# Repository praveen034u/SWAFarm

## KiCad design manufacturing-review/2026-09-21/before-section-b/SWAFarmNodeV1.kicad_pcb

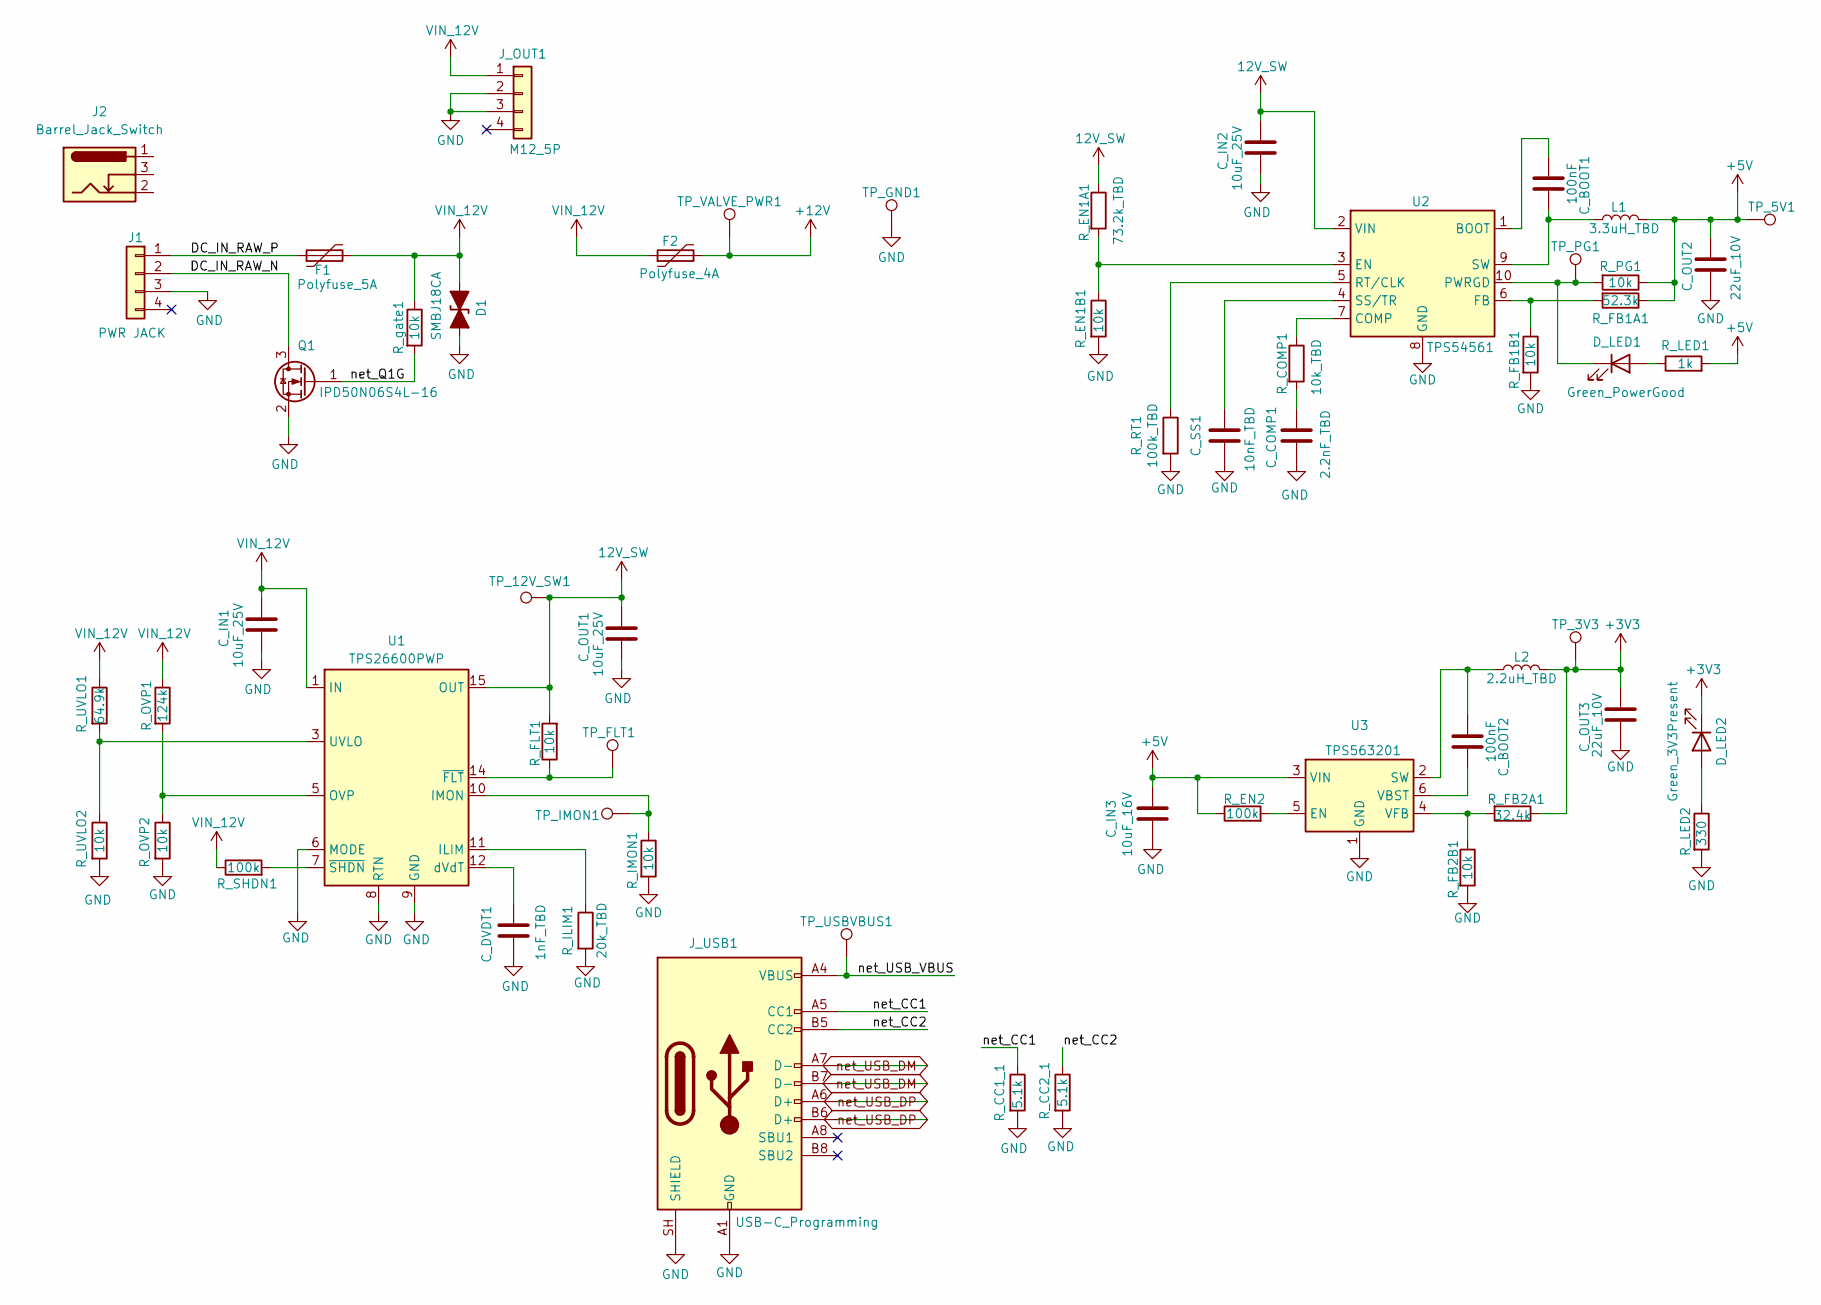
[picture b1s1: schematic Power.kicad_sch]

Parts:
C_BOOT1, C_BOOT2: 100nF; C_0603_1608Metric
C_COMP1: 2.2nF_TBD; C_0603_1608Metric
C_DVDT1: 1nF_TBD; C_0805_2012Metric
C_IN1, C_IN2: 10uF_25V; C_1206_3216Metric
C_IN3: 10uF_16V; C_1206_3216Metric
C_OUT1: 10uF_25V; C_1206_3216Metric
C_OUT2, C_OUT3: 22uF_10V; C_1206_3216Metric
C_SS1: 10nF_TBD; C_0603_1608Metric
D1: SMBJ18CA; D_SMB
D_LED1: Green_PowerGood; LED_0805_2012Metric
D_LED2: Green_3V3Present; LED_0805_2012Metric
F1: Polyfuse_5A; Fuse_1812_4532Metric
F2: Polyfuse_4A; Fuse_1812_4532Metric
J1: PWR JACK; PinHeader_1x04_P2.54mm_Vertical
J2: Barrel_Jack_Switch
J_OUT1: M12_5P; PinHeader_1x04_P2.54mm_Vertical
J_USB1: USB-C_Programming; USB_C_Receptacle_HRO_TYPE-C-31-M-12
L1: 3.3uH_TBD; L_Bourns-SRN6028
L2: 2.2uH_TBD; L_Bourns-SRN4018
Q1: IPD50N06S4L-16; SOT-23
R_CC1_1, R_CC2_1: 5.1k; R_0805_2012Metric
R_COMP1: 10k_TBD; R_0805_2012Metric
R_EN1A1: 73.2k_TBD; R_0805_2012Metric
R_EN1B1: 10k; R_0805_2012Metric
R_EN2: 100k; R_0805_2012Metric
R_FB1A1: 52.3k; R_0805_2012Metric
R_FB1B1, R_FB2B1: 10k; R_0805_2012Metric
R_FB2A1: 32.4k; R_0805_2012Metric
R_FLT1: 10k; R_0805_2012Metric
R_ILIM1: 20k_TBD; R_0805_2012Metric
R_IMON1: 10k; R_0805_2012Metric
R_LED1: 1k; R_0805_2012Metric
R_LED2: 330; R_0805_2012Metric
R_OVP1: 124k; R_0805_2012Metric
R_OVP2: 10k; R_0805_2012Metric
R_PG1: 10k; R_0805_2012Metric
R_RT1: 100k_TBD; R_0805_2012Metric
R_SHDN1: 100k; R_0805_2012Metric
R_UVLO1: 64.9k; R_0805_2012Metric
R_UVLO2: 10k; R_0805_2012Metric
R_gate1: 10k; R_0805_2012Metric
TP_3V3: V3V3_RAIL; TestPoint_Pad_D1.5mm
TP_5V1: V5_RAIL; TestPoint_Pad_D1.5mm
TP_12V_SW1: V12_SW; TestPoint_Pad_D1.5mm
TP_FLT1: nFLT; TestPoint_Pad_D1.5mm
TP_GND1: GND; TestPoint_Pad_D1.5mm
TP_IMON1: IMON; TestPoint_Pad_D1.5mm
TP_PG1: nPWRGD; TestPoint_Pad_D1.5mm
TP_USBVBUS1: USB_VBUS; TestPoint_Pad_D1.5mm
TP_VALVE_PWR1: V12_VALVE; TestPoint_Pad_D1.5mm
U1: TPS26600PWP; HTSSOP-16-1EP_4.4x5mm_P0.65mm_EP3.4x5mm_Mask2.66x2.46mm_The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
U2: TPS54561; WSON-10-1EP_4x4mm_P0.8mm_EP2.6x3mm_ThermalVias
U3: TPS563201; SOT-23-6

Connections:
12V_SW: C_IN2.1, C_OUT1.1, R_EN1A1.1, R_FLT1.2, TP_12V_SW1.1 (1_1), U1.15 (OUT), U1.16 (OUT), U2.2 (VIN)
+3V3: C_OUT3.1, D_LED2.1 (K), L2.2, R_FB2A1.1, TP_3V3.1 (1_1); also elsewhere on the board
+5V: C_IN3.1, C_OUT2.1, L1.2, R_EN2.1, R_FB1A1.1, R_LED1.2, R_PG1.1, TP_5V1.1 (1_1), U3.3 (VIN); also elsewhere on the board
+12V: F2.2, TP_VALVE_PWR1.1 (1_1); also elsewhere on the board
/Power/DC_IN_RAW_N: J1.2, Q1.3 (D)
/Power/DC_IN_RAW_P: F1.1, J1.1
/Power/net_CC1: J_USB1.A5 (CC1), R_CC1_1.1
/Power/net_CC2: J_USB1.B5 (CC2), R_CC2_1.1
/Power/net_Q1G: Q1.1 (G), R_gate1.2
/Power/net_USB_VBUS: J_USB1.A4 (VBUS), J_USB1.A9 (VBUS), J_USB1.B4 (VBUS), J_USB1.B9 (VBUS), TP_USBVBUS1.1 (1_1)
GND: C_COMP1.2, C_DVDT1.2, C_IN1.2, C_IN2.2, C_IN3.2, C_OUT1.2, C_OUT2.2, C_OUT3.2, C_SS1.2, D1.2 (A2), J1.3, J_OUT1.2, J_OUT1.3, J_USB1.A1 (GND), J_USB1.A12 (GND), J_USB1.B1 (GND), J_USB1.B12 (GND), J_USB1.SH (SHIELD), Q1.2 (S), R_CC1_1.2, R_CC2_1.2, R_EN1B1.2, R_FB1B1.2, R_FB2B1.2, R_ILIM1.2, R_IMON1.2, R_LED2.2, R_OVP2.2, R_RT1.2, R_UVLO2.2, TP_GND1.1 (1_1), U1.6 (MODE), U1.8 (RTN), U1.9 (GND), U1.17 (RTN), U2.8 (GND), U2.11 (GND), U3.1 (GND); also elsewhere on the board
unnamed: C_COMP1.1, R_COMP1.2
unnamed: D_LED1.2 (A), R_LED1.1
unnamed: D_LED1.1 (K), R_PG1.2, TP_PG1.1 (1_1), U2.10 (PWRGD)
unnamed: D_LED2.2 (A), R_LED2.1
unnamed: R_ILIM1.1, U1.11 (ILIM)
unnamed: R_IMON1.1, TP_IMON1.1 (1_1), U1.10 (IMON)
unnamed: R_OVP1.2, R_OVP2.1, U1.5 (OVP)
unnamed: R_UVLO1.2, R_UVLO2.1, U1.3 (UVLO)
unnamed: C_DVDT1.1, U1.12 (dVdT)
unnamed: R_FLT1.1, TP_FLT1.1 (1_1), U1.14 (~FLT)
unnamed: R_SHDN1.2, U1.7 (~SHDN)
unnamed: C_BOOT1.1, U2.1 (BOOT)
unnamed: R_COMP1.1, U2.7 (COMP)
unnamed: R_EN1A1.2, R_EN1B1.1, U2.3 (EN)
unnamed: R_FB1A1.2, R_FB1B1.1, U2.6 (FB)
unnamed: R_RT1.1, U2.5 (RT/CLK)
unnamed: C_SS1.1, U2.4 (SS/TR)
unnamed: C_BOOT1.2, L1.1, U2.9 (SW)
unnamed: R_EN2.2, U3.5 (EN)
unnamed: C_BOOT2.2, L2.1, U3.2 (SW)
unnamed: C_BOOT2.1, U3.6 (VBST)
unnamed: R_FB2A1.2, R_FB2B1.1, U3.4 (VFB)
VIN_12V: C_IN1.1, D1.1 (A1), F1.2, F2.1, J_OUT1.1, R_OVP1.1, R_SHDN1.1, R_UVLO1.1, R_gate1.1, U1.1 (IN), U1.2 (IN)
net_USB_DM: J_USB1.A7 (D-), J_USB1.B7 (D-); also elsewhere on the board
net_USB_DP: J_USB1.A6 (D+), J_USB1.B6 (D+); also elsewhere on the board

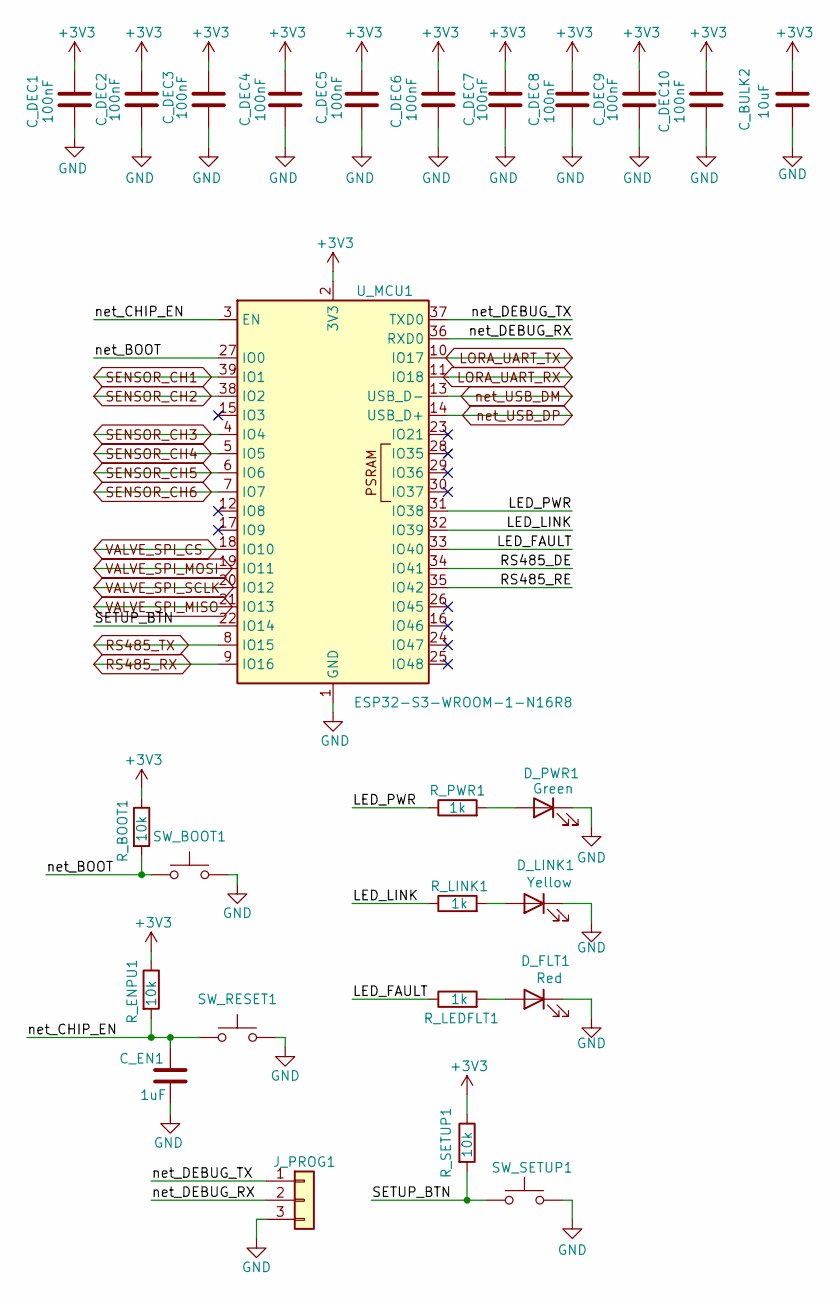
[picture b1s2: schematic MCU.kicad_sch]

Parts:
C_BULK2: 10uF; C_1206_3216Metric
C_DEC1, C_DEC2, C_DEC3, C_DEC4, C_DEC5, C_DEC6, C_DEC7, C_DEC8, C_DEC9, C_DEC10: 100nF; C_0603_1608Metric
C_EN1: 1uF; C_0805_2012Metric
D_FLT1: Red; LED_0805_2012Metric
D_LINK1: Yellow; LED_0805_2012Metric
D_PWR1: Green; LED_0805_2012Metric
J_PROG1: Debug_UART_TX_RX_GND; PinHeader_1x03_P2.54mm_Vertical
R_BOOT1: 10k; R_0805_2012Metric
R_ENPU1: 10k; R_0805_2012Metric
R_LEDFLT1: 1k; R_0805_2012Metric
R_LINK1: 1k; R_0805_2012Metric
R_PWR1: 1k; R_0805_2012Metric
R_SETUP1: 10k; R_0805_2012Metric
SW_BOOT1: BOOT; SW_SPST_B3U-1000P
SW_RESET1: RESET; SW_SPST_B3U-1000P
SW_SETUP1: SETUP; SW_SPST_B3U-1000P
U_MCU1: ESP32-S3-WROOM-1-N16R8; ESP32-S3-WROOM-1

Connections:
+3V3: C_BULK2.1, C_DEC1.1, C_DEC2.1, C_DEC3.1, C_DEC4.1, C_DEC5.1, C_DEC6.1, C_DEC7.1, C_DEC8.1, C_DEC9.1, C_DEC10.1, R_BOOT1.1, R_ENPU1.1, R_SETUP1.1, U_MCU1.2 (3V3); also elsewhere on the board
/MCU/LED_FAULT: R_LEDFLT1.1, U_MCU1.33 (IO40)
/MCU/LED_LINK: R_LINK1.1, U_MCU1.32 (IO39)
/MCU/LED_PWR: R_PWR1.1, U_MCU1.31 (IO38)
/MCU/RS485_DE: U_MCU1.34 (IO41)
/MCU/RS485_RE: U_MCU1.35 (IO42)
/MCU/SETUP_BTN: R_SETUP1.2, SW_SETUP1.1, U_MCU1.22 (IO14)
/MCU/net_BOOT: R_BOOT1.2, SW_BOOT1.1, U_MCU1.27 (IO0)
/MCU/net_CHIP_EN: C_EN1.1, R_ENPU1.2, SW_RESET1.1, U_MCU1.3 (EN)
/MCU/net_DEBUG_RX: J_PROG1.2, U_MCU1.36 (RXD0)
/MCU/net_DEBUG_TX: J_PROG1.1, U_MCU1.37 (TXD0)
GND: C_BULK2.2, C_DEC1.2, C_DEC2.2, C_DEC3.2, C_DEC4.2, C_DEC5.2, C_DEC6.2, C_DEC7.2, C_DEC8.2, C_DEC9.2, C_DEC10.2, C_EN1.2, D_FLT1.1 (K), D_LINK1.1 (K), D_PWR1.1 (K), J_PROG1.3, SW_BOOT1.2, SW_RESET1.2, SW_SETUP1.2, U_MCU1.1 (GND), U_MCU1.40 (GND), U_MCU1.41 (GND); also elsewhere on the board
LORA_UART_RX: U_MCU1.11 (IO18); also elsewhere on the board
LORA_UART_TX: U_MCU1.10 (IO17); also elsewhere on the board
unnamed: D_FLT1.2 (A), R_LEDFLT1.2
unnamed: D_LINK1.2 (A), R_LINK1.2
unnamed: D_PWR1.2 (A), R_PWR1.2
RS485_RX: U_MCU1.9 (IO16); also elsewhere on the board
RS485_TX: U_MCU1.8 (IO15); also elsewhere on the board
SENSOR_CH1: U_MCU1.39 (IO1); also elsewhere on the board
SENSOR_CH2: U_MCU1.38 (IO2); also elsewhere on the board
SENSOR_CH3: U_MCU1.4 (IO4); also elsewhere on the board
SENSOR_CH4: U_MCU1.5 (IO5); also elsewhere on the board
SENSOR_CH5: U_MCU1.6 (IO6); also elsewhere on the board
SENSOR_CH6: U_MCU1.7 (IO7); also elsewhere on the board
VALVE_SPI_CS: U_MCU1.18 (IO10); also elsewhere on the board
VALVE_SPI_MISO: U_MCU1.21 (IO13); also elsewhere on the board
VALVE_SPI_MOSI: U_MCU1.19 (IO11); also elsewhere on the board
VALVE_SPI_SCLK: U_MCU1.20 (IO12); also elsewhere on the board
net_USB_DM: U_MCU1.13 (USB_D-); also elsewhere on the board
net_USB_DP: U_MCU1.14 (USB_D+); also elsewhere on the board

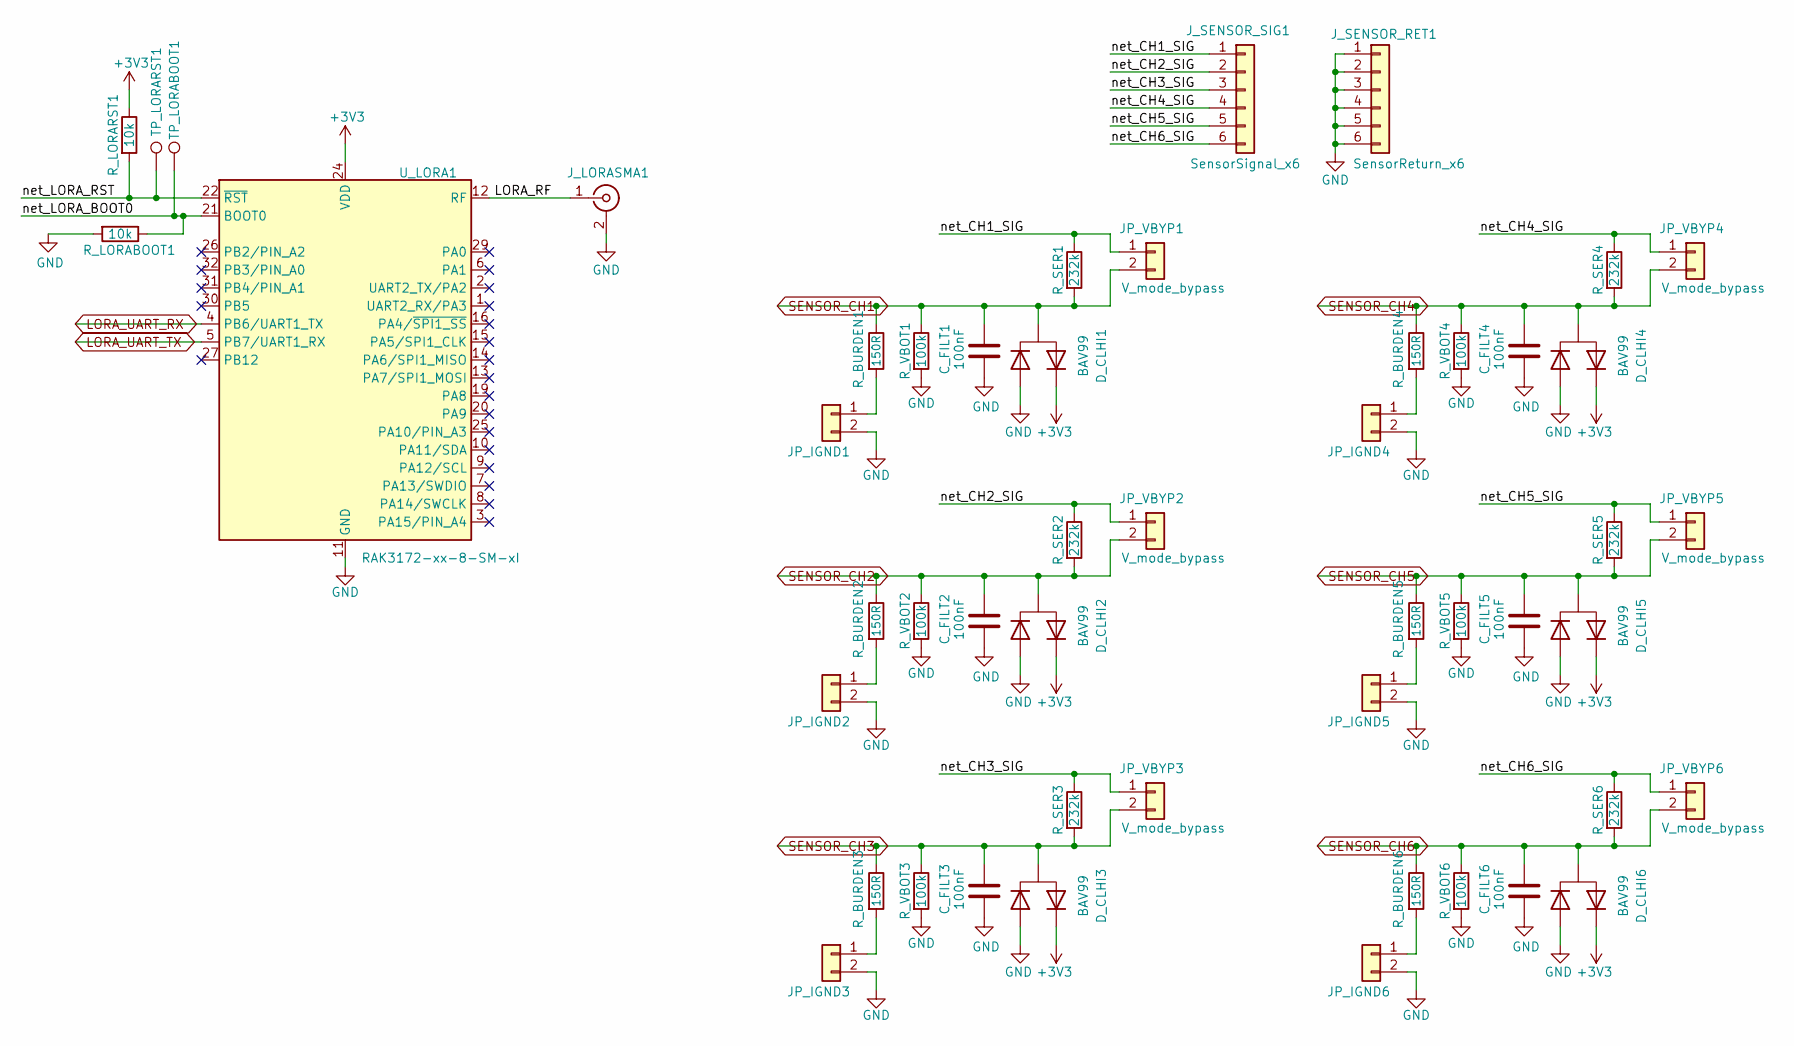
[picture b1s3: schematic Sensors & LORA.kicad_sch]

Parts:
C_FILT1, C_FILT2, C_FILT3, C_FILT4, C_FILT5, C_FILT6: 100nF; C_0603_1608Metric
D_CLHI1, D_CLHI2, D_CLHI3, D_CLHI4, D_CLHI5, D_CLHI6: BAV99; SOT-23
JP_IGND1, JP_IGND2, JP_IGND3, JP_IGND4, JP_IGND5, JP_IGND6: I_mode_gnd; PinHeader_1x02_P2.54mm_Vertical
JP_VBYP1, JP_VBYP2, JP_VBYP3, JP_VBYP4, JP_VBYP5, JP_VBYP6: V_mode_bypass; PinHeader_1x02_P2.54mm_Vertical
J_LORASMA1: SMA_Bulkhead_Antenna; SMA_Amphenol_132134_Vertical
J_SENSOR_RET1: SensorReturn_x6; TerminalBlock_Phoenix_MKDS-1,5-6-5.08_1x06_P5.08mm_Horizont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
J_SENSOR_SIG1: SensorSignal_x6; TerminalBlock_Phoenix_MKDS-1,5-6-5.08_1x06_P5.08mm_Horizont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
R_BURDEN1, R_BURDEN2, R_BURDEN3, R_BURDEN4, R_BURDEN5, R_BURDEN6: 150R; R_0805_2012Metric
R_LORABOOT1: 10k; R_0805_2012Metric
R_LORARST1: 10k; R_0805_2012Metric
R_SER1, R_SER2, R_SER3, R_SER4, R_SER5, R_SER6: 232k; R_0805_2012Metric
R_VBOT1, R_VBOT2, R_VBOT3, R_VBOT4, R_VBOT5, R_VBOT6: 100k; R_0805_2012Metric
TP_LORABOOT1: LORA_BOOT0; TestPoint_Pad_D1.5mm
TP_LORARST1: LORA_RESET; TestPoint_Pad_D1.5mm
U_LORA1: RAK3172-xx-8-SM-xI; RAK3172

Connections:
+3V3: D_CLHI1.2 (S), D_CLHI2.2 (S), D_CLHI3.2 (S), D_CLHI4.2 (S), D_CLHI5.2 (S), D_CLHI6.2 (S), R_LORARST1.1, U_LORA1.24 (VDD); also elsewhere on the board
/Sensors & LORA/LORA_RF: J_LORASMA1.1 (In), U_LORA1.12 (RF)
/Sensors & LORA/net_CH1_SIG: JP_VBYP1.1, J_SENSOR_SIG1.1, R_SER1.1
/Sensors & LORA/net_CH2_SIG: JP_VBYP2.1, J_SENSOR_SIG1.2, R_SER2.1
/Sensors & LORA/net_CH3_SIG: JP_VBYP3.1, J_SENSOR_SIG1.3, R_SER3.1
/Sensors & LORA/net_CH4_SIG: JP_VBYP4.1, J_SENSOR_SIG1.4, R_SER4.1
/Sensors & LORA/net_CH5_SIG: JP_VBYP5.1, J_SENSOR_SIG1.5, R_SER5.1
/Sensors & LORA/net_CH6_SIG: JP_VBYP6.1, J_SENSOR_SIG1.6, R_SER6.1
/Sensors & LORA/net_LORA_BOOT0: R_LORABOOT1.1, TP_LORABOOT1.1 (1_1), U_LORA1.21 (BOOT0)
/Sensors & LORA/net_LORA_RST: R_LORARST1.2, TP_LORARST1.1 (1_1), U_LORA1.22 (~RST)
GND: C_FILT1.2, C_FILT2.2, C_FILT3.2, C_FILT4.2, C_FILT5.2, C_FILT6.2, D_CLHI1.1 (G), D_CLHI2.1 (G), D_CLHI3.1 (G), D_CLHI4.1 (G), D_CLHI5.1 (G), D_CLHI6.1 (G), JP_IGND1.2, JP_IGND2.2, JP_IGND3.2, JP_IGND4.2, JP_IGND5.2, JP_IGND6.2, J_LORASMA1.2 (Ext), J_SENSOR_RET1.1, J_SENSOR_RET1.2, J_SENSOR_RET1.3, J_SENSOR_RET1.4, J_SENSOR_RET1.5, J_SENSOR_RET1.6, R_LORABOOT1.2, R_VBOT1.2, R_VBOT2.2, R_VBOT3.2, R_VBOT4.2, R_VBOT5.2, R_VBOT6.2, U_LORA1.11 (GND), U_LORA1.17 (GND), U_LORA1.18 (GND), U_LORA1.23 (GND), U_LORA1.28 (GND); also elsewhere on the board
LORA_UART_RX: U_LORA1.4 (PB6/UART1_TX); also elsewhere on the board
LORA_UART_TX: U_LORA1.5 (PB7/UART1_RX); also elsewhere on the board
unnamed: JP_IGND1.1, R_BURDEN1.2
unnamed: JP_IGND2.1, R_BURDEN2.2
unnamed: JP_IGND3.1, R_BURDEN3.2
unnamed: JP_IGND4.1, R_BURDEN4.2
unnamed: JP_IGND5.1, R_BURDEN5.2
unnamed: JP_IGND6.1, R_BURDEN6.2
SENSOR_CH1: C_FILT1.1, D_CLHI1.3 (D), JP_VBYP1.2, R_BURDEN1.1, R_SER1.2, R_VBOT1.1; also elsewhere on the board
SENSOR_CH2: C_FILT2.1, D_CLHI2.3 (D), JP_VBYP2.2, R_BURDEN2.1, R_SER2.2, R_VBOT2.1; also elsewhere on the board
SENSOR_CH3: C_FILT3.1, D_CLHI3.3 (D), JP_VBYP3.2, R_BURDEN3.1, R_SER3.2, R_VBOT3.1; also elsewhere on the board
SENSOR_CH4: C_FILT4.1, D_CLHI4.3 (D), JP_VBYP4.2, R_BURDEN4.1, R_SER4.2, R_VBOT4.1; also elsewhere on the board
SENSOR_CH5: C_FILT5.1, D_CLHI5.3 (D), JP_VBYP5.2, R_BURDEN5.1, R_SER5.2, R_VBOT5.1; also elsewhere on the board
SENSOR_CH6: C_FILT6.1, D_CLHI6.3 (D), JP_VBYP6.2, R_BURDEN6.1, R_SER6.2, R_VBOT6.1; also elsewhere on the board

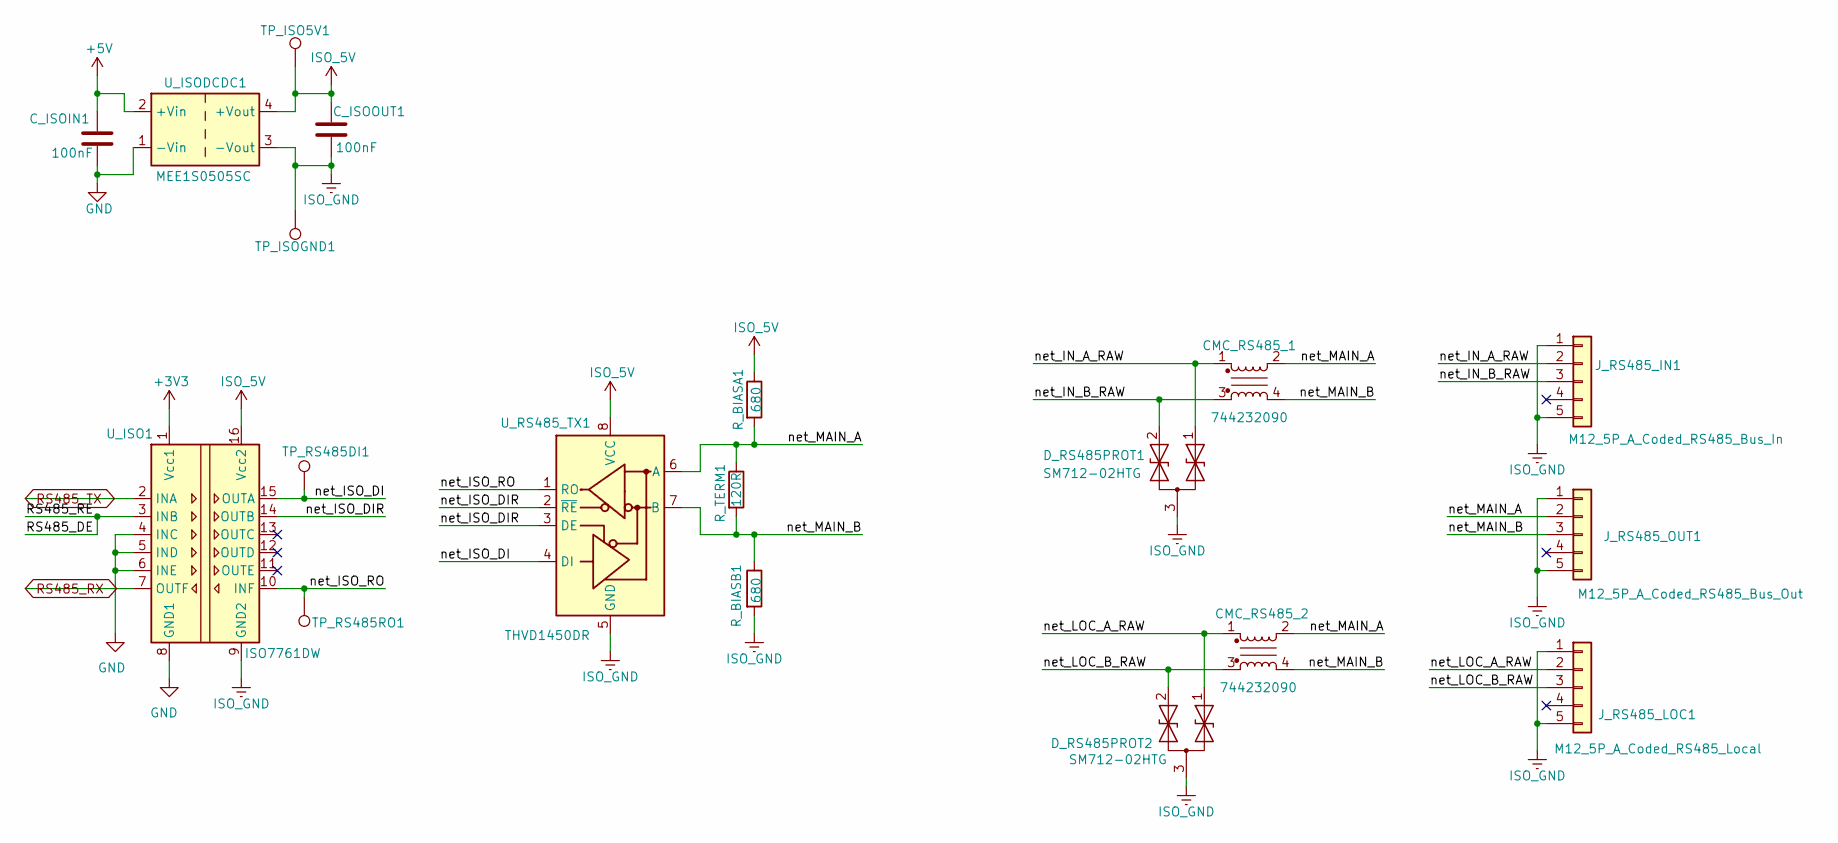
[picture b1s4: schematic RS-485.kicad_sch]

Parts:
CMC_RS485_1, CMC_RS485_2: 744232090; L_CommonModeChoke_Bourns_SRF1260
C_ISOIN1: 100nF; C_0603_1608Metric
C_ISOOUT1: 100nF; C_0603_1608Metric
D_RS485PROT1, D_RS485PROT2: SM712-02HTG; SOT-23
J_RS485_IN1: M12_5P_A_Coded_RS485_Bus_In; PinHeader_1x05_P2.54mm_Vertical
J_RS485_LOC1: M12_5P_A_Coded_RS485_Local; PinHeader_1x05_P2.54mm_Vertical
J_RS485_OUT1: M12_5P_A_Coded_RS485_Bus_Out; PinHeader_1x05_P2.54mm_Vertical
R_BIASA1: 680; R_0805_2012Metric
R_BIASB1: 680; R_0805_2012Metric
R_TERM1: 120R; R_0805_2012Metric
TP_ISO5V1: ISO_5V; TestPoint_Pad_D1.5mm
TP_ISOGND1: ISO_GND; TestPoint_Pad_D1.5mm
TP_RS485DI1: ISO_DI; TestPoint_Pad_D1.5mm
TP_RS485RO1: ISO_RO; TestPoint_Pad_D1.5mm
U_ISO1: ISO7761DW; SOIC-16W_7.5x10.3mm_P1.27mm
U_ISODCDC1: MEE1S0505SC; Converter_DCDC_Murata_MEE1SxxxxSC_THT
U_RS485_TX1: THVD1450DR; SOIC-8_3.9x4.9mm_P1.27mm

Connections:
+3V3: U_ISO1.1 (Vcc1); also elsewhere on the board
+5V: C_ISOIN1.1, U_ISODCDC1.2 (+Vin); also elsewhere on the board
/RS-485/RS485_DE: U_ISO1.3 (INB)
/RS-485/net_IN_A_RAW: CMC_RS485_1.1, D_RS485PROT1.1 (A1), J_RS485_IN1.2
/RS-485/net_IN_B_RAW: CMC_RS485_1.3, D_RS485PROT1.2 (A2), J_RS485_IN1.3
/RS-485/net_ISO_DI: TP_RS485DI1.1 (1_1), U_ISO1.15 (OUTA), U_RS485_TX1.4 (DI)
/RS-485/net_ISO_DIR: U_ISO1.14 (OUTB), U_RS485_TX1.2 (~RE), U_RS485_TX1.3 (DE)
/RS-485/net_ISO_RO: TP_RS485RO1.1 (1_1), U_ISO1.10 (INF), U_RS485_TX1.1 (RO)
/RS-485/net_LOC_A_RAW: CMC_RS485_2.1, D_RS485PROT2.1 (A1), J_RS485_LOC1.2
/RS-485/net_LOC_B_RAW: CMC_RS485_2.3, D_RS485PROT2.2 (A2), J_RS485_LOC1.3
/RS-485/net_MAIN_A: CMC_RS485_1.2, CMC_RS485_2.2, J_RS485_OUT1.2, R_BIASA1.2, R_TERM1.1, U_RS485_TX1.6 (A)
/RS-485/net_MAIN_B: CMC_RS485_1.4, CMC_RS485_2.4, J_RS485_OUT1.3, R_BIASB1.1, R_TERM1.2, U_RS485_TX1.7 (B)
GND: C_ISOIN1.2, U_ISO1.4 (INC), U_ISO1.5 (IND), U_ISO1.6 (INE), U_ISO1.8 (GND1), U_ISODCDC1.1 (-Vin); also elsewhere on the board
ISO_5V: C_ISOOUT1.1, R_BIASA1.1, TP_ISO5V1.1 (1_1), U_ISO1.16 (Vcc2), U_ISODCDC1.4 (+Vout), U_RS485_TX1.8 (VCC)
ISO_GND: C_ISOOUT1.2, D_RS485PROT1.3 (common), D_RS485PROT2.3 (common), J_RS485_IN1.1, J_RS485_IN1.5, J_RS485_LOC1.1, J_RS485_LOC1.5, J_RS485_OUT1.1, J_RS485_OUT1.5, R_BIASB1.2, TP_ISOGND1.1 (1_1), U_ISO1.9 (GND2), U_ISODCDC1.3 (-Vout), U_RS485_TX1.5 (GND)
RS485_RX: U_ISO1.7 (OUTF); also elsewhere on the board
RS485_TX: U_ISO1.2 (INA); also elsewhere on the board

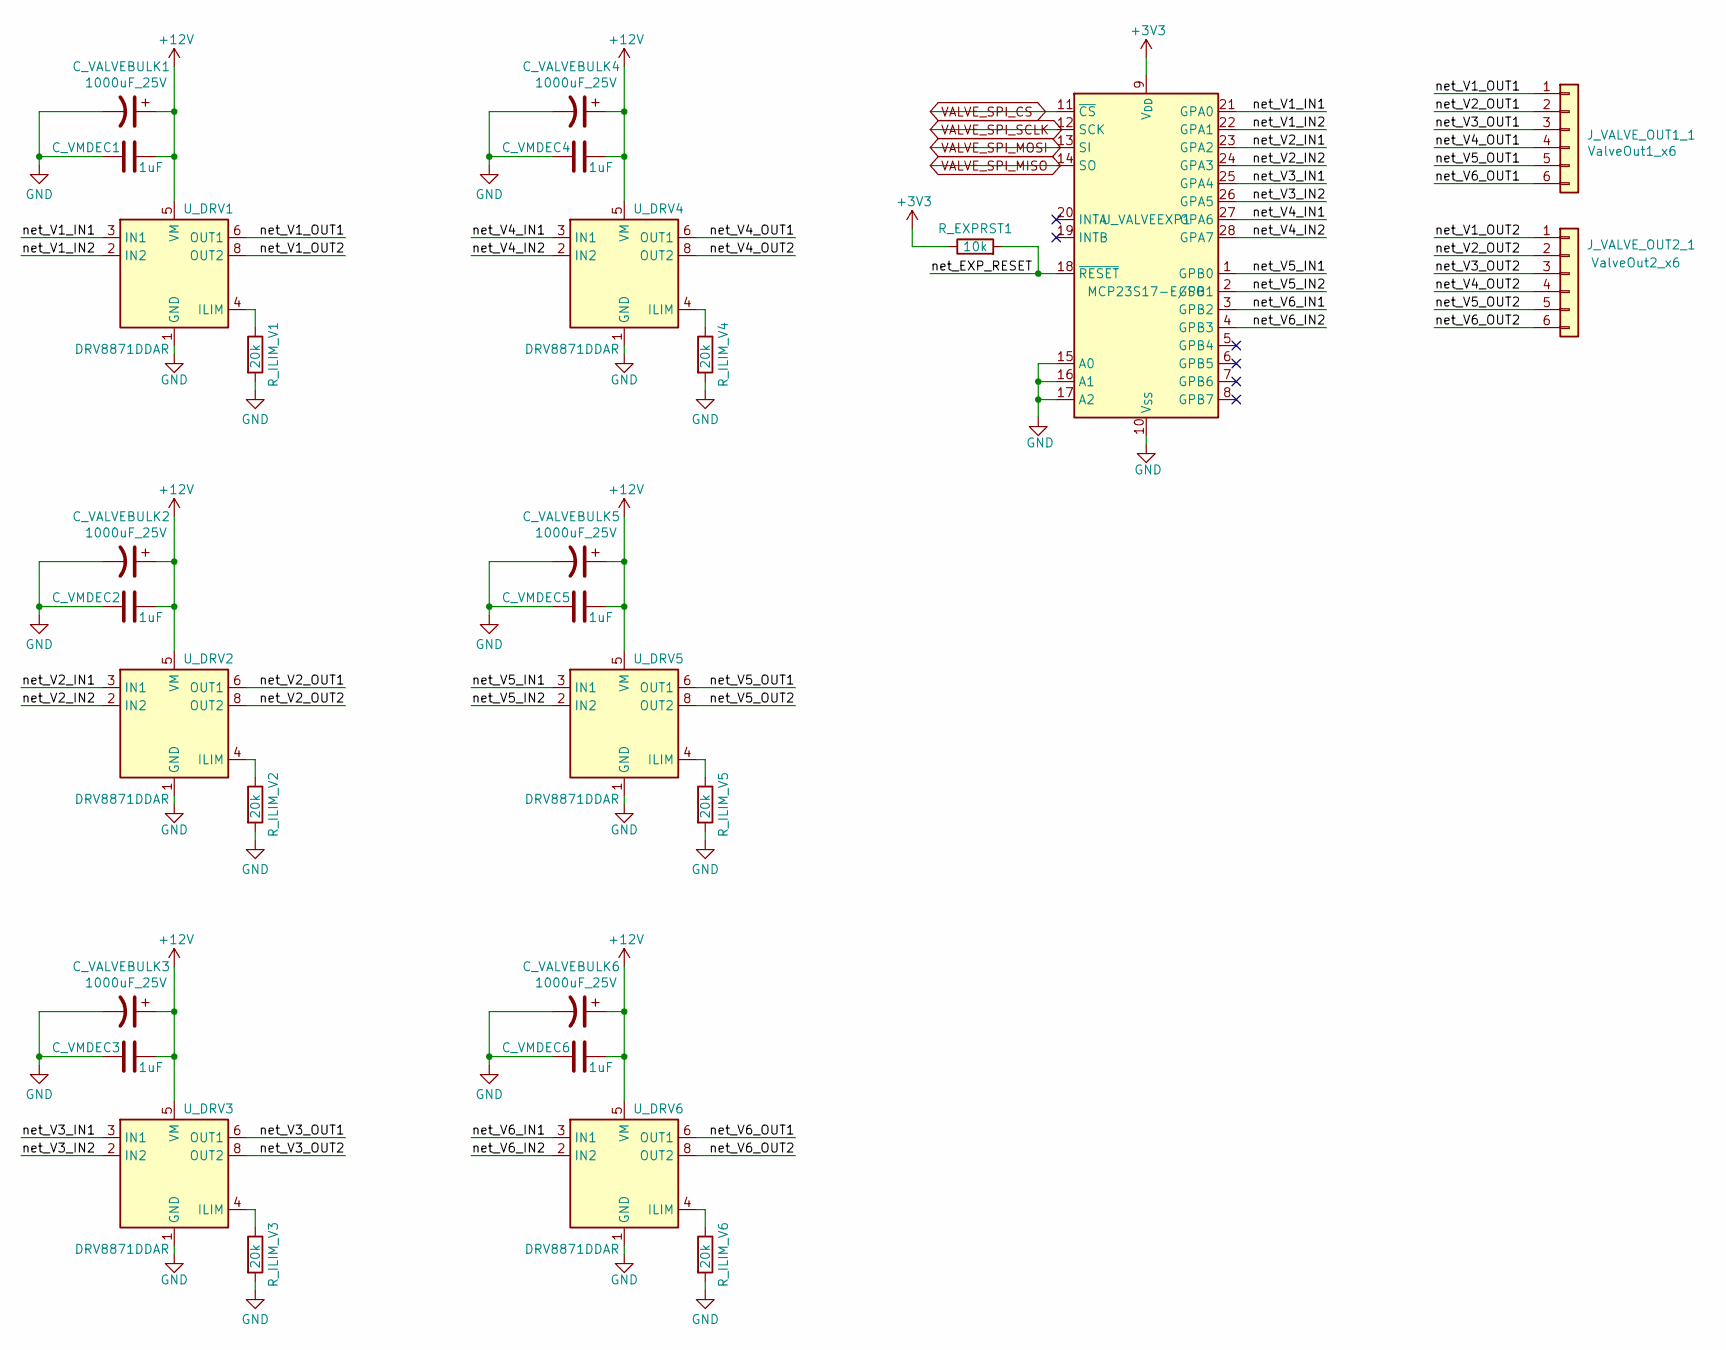
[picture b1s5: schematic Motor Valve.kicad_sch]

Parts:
C_VALVEBULK1, C_VALVEBULK2, C_VALVEBULK3, C_VALVEBULK4, C_VALVEBULK5, C_VALVEBULK6: 1000uF_25V; CP_Radial_D12.5mm_P5.00mm
C_VMDEC1, C_VMDEC2, C_VMDEC3, C_VMDEC4, C_VMDEC5, C_VMDEC6: 1uF; C_0805_2012Metric
J_VALVE_OUT1_1: ValveOut1_x6; TerminalBlock_Phoenix_MKDS-1,5-6-5.08_1x06_P5.08mm_Horizont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
J_VALVE_OUT2_1: ValveOut2_x6; TerminalBlock_Phoenix_MKDS-1,5-6-5.08_1x06_P5.08mm_Horizont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
R_EXPRST1: 10k; R_0805_2012Metric
R_ILIM_V1, R_ILIM_V2, R_ILIM_V3, R_ILIM_V4, R_ILIM_V5, R_ILIM_V6: 20k; R_0805_2012Metric
U_DRV1, U_DRV2, U_DRV3, U_DRV4, U_DRV5, U_DRV6: DRV8871DDAR; TI_SO-PowerPAD-8_ThermalVias
U_VALVEEXP1: MCP23S17-E/SO; SOIC-28W_7.5x17.9mm_P1.27mm

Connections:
+3V3: R_EXPRST1.1, U_VALVEEXP1.9 (V_{DD}); also elsewhere on the board
+12V: C_VALVEBULK1.1, C_VALVEBULK2.1, C_VALVEBULK3.1, C_VALVEBULK4.1, C_VALVEBULK5.1, C_VALVEBULK6.1, C_VMDEC1.1, C_VMDEC2.1, C_VMDEC3.1, C_VMDEC4.1, C_VMDEC5.1, C_VMDEC6.1, U_DRV1.5 (VM), U_DRV2.5 (VM), U_DRV3.5 (VM), U_DRV4.5 (VM), U_DRV5.5 (VM), U_DRV6.5 (VM); also elsewhere on the board
/Motor Valve/net_EXP_RESET: R_EXPRST1.2, U_VALVEEXP1.18 (~RESET)
/Motor Valve/net_V1_IN1: U_DRV1.3 (IN1), U_VALVEEXP1.21 (GPA0)
/Motor Valve/net_V1_IN2: U_DRV1.2 (IN2), U_VALVEEXP1.22 (GPA1)
/Motor Valve/net_V1_OUT1: J_VALVE_OUT1_1.1, U_DRV1.6 (OUT1)
/Motor Valve/net_V1_OUT2: J_VALVE_OUT2_1.1, U_DRV1.8 (OUT2)
/Motor Valve/net_V2_IN1: U_DRV2.3 (IN1), U_VALVEEXP1.23 (GPA2)
/Motor Valve/net_V2_IN2: U_DRV2.2 (IN2), U_VALVEEXP1.24 (GPA3)
/Motor Valve/net_V2_OUT1: J_VALVE_OUT1_1.2, U_DRV2.6 (OUT1)
/Motor Valve/net_V2_OUT2: J_VALVE_OUT2_1.2, U_DRV2.8 (OUT2)
/Motor Valve/net_V3_IN1: U_DRV3.3 (IN1), U_VALVEEXP1.25 (GPA4)
/Motor Valve/net_V3_IN2: U_DRV3.2 (IN2), U_VALVEEXP1.26 (GPA5)
/Motor Valve/net_V3_OUT1: J_VALVE_OUT1_1.3, U_DRV3.6 (OUT1)
/Motor Valve/net_V3_OUT2: J_VALVE_OUT2_1.3, U_DRV3.8 (OUT2)
/Motor Valve/net_V4_IN1: U_DRV4.3 (IN1), U_VALVEEXP1.27 (GPA6)
/Motor Valve/net_V4_IN2: U_DRV4.2 (IN2), U_VALVEEXP1.28 (GPA7)
/Motor Valve/net_V4_OUT1: J_VALVE_OUT1_1.4, U_DRV4.6 (OUT1)
/Motor Valve/net_V4_OUT2: J_VALVE_OUT2_1.4, U_DRV4.8 (OUT2)
/Motor Valve/net_V5_IN1: U_DRV5.3 (IN1), U_VALVEEXP1.1 (GPB0)
/Motor Valve/net_V5_IN2: U_DRV5.2 (IN2), U_VALVEEXP1.2 (GPB1)
/Motor Valve/net_V5_OUT1: J_VALVE_OUT1_1.5, U_DRV5.6 (OUT1)
/Motor Valve/net_V5_OUT2: J_VALVE_OUT2_1.5, U_DRV5.8 (OUT2)
/Motor Valve/net_V6_IN1: U_DRV6.3 (IN1), U_VALVEEXP1.3 (GPB2)
/Motor Valve/net_V6_IN2: U_DRV6.2 (IN2), U_VALVEEXP1.4 (GPB3)
/Motor Valve/net_V6_OUT1: J_VALVE_OUT1_1.6, U_DRV6.6 (OUT1)
/Motor Valve/net_V6_OUT2: J_VALVE_OUT2_1.6, U_DRV6.8 (OUT2)
GND: C_VALVEBULK1.2, C_VALVEBULK2.2, C_VALVEBULK3.2, C_VALVEBULK4.2, C_VALVEBULK5.2, C_VALVEBULK6.2, C_VMDEC1.2, C_VMDEC2.2, C_VMDEC3.2, C_VMDEC4.2, C_VMDEC5.2, C_VMDEC6.2, R_ILIM_V1.2, R_ILIM_V2.2, R_ILIM_V3.2, R_ILIM_V4.2, R_ILIM_V5.2, R_ILIM_V6.2, U_DRV1.1 (GND), U_DRV1.7 (GND), U_DRV1.9 (GND), U_DRV2.1 (GND), U_DRV2.7 (GND), U_DRV2.9 (GND), U_DRV3.1 (GND), U_DRV3.7 (GND), U_DRV3.9 (GND), U_DRV4.1 (GND), U_DRV4.7 (GND), U_DRV4.9 (GND), U_DRV5.1 (GND), U_DRV5.7 (GND), U_DRV5.9 (GND), U_DRV6.1 (GND), U_DRV6.7 (GND), U_DRV6.9 (GND), U_VALVEEXP1.10 (V_{SS}), U_VALVEEXP1.15 (A0), U_VALVEEXP1.16 (A1), U_VALVEEXP1.17 (A2); also elsewhere on the board
unnamed: R_ILIM_V1.1, U_DRV1.4 (ILIM)
unnamed: R_ILIM_V2.1, U_DRV2.4 (ILIM)
unnamed: R_ILIM_V3.1, U_DRV3.4 (ILIM)
unnamed: R_ILIM_V4.1, U_DRV4.4 (ILIM)
unnamed: R_ILIM_V5.1, U_DRV5.4 (ILIM)
unnamed: R_ILIM_V6.1, U_DRV6.4 (ILIM)
VALVE_SPI_CS: U_VALVEEXP1.11 (~CS); also elsewhere on the board
VALVE_SPI_MISO: U_VALVEEXP1.14 (SO); also elsewhere on the board
VALVE_SPI_MOSI: U_VALVEEXP1.13 (SI); also elsewhere on the board
VALVE_SPI_SCLK: U_VALVEEXP1.12 (SCK); also elsewhere on the board

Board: 4 copper layers, 184 parts (0 on the bottom side), 118 nets, no tracks yet.

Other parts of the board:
MH1, MH2, MH3, MH4: MountingHole_3.2mm_M3
